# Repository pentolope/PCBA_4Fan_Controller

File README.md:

# Four-Fan PWM/Tach Controller

Board that powers and controls four standard 4-wire 12 V PC fans, with a microcontroller giving independent PWM and tach per fan from a single 12 V input.

This repository holds the design problem for a four-channel PC fan controller. The brief fixes the function and almost nothing else: four standard 4-wire 12 V PC fans are powered and controlled from the board, a microcontroller generates independent PWM and reads independent tach signals, the board accepts a single 12 V input and derives its logic power locally, protection is required, and a simple host interface is to be provided. It also asks that the board be kept compact and serviceable, without stating any dimension, outline, or mounting scheme.

At brief detail 1/5, everything below that statement of function is left to the design agent: microcontroller family, logic rail voltage and regulator topology, host interface protocol and physical connection, how the fans and the 12 V input attach to the board, per-fan current budget, what "sensible protection" concretely covers, board outline, and stackup. Those choices belong in the design record as decisions with rationale, not as requirements attributed to the brief.

> **This board has not been designed.** There is no schematic, no layout and no
> part selection here — only the brief, a reading of the brief, and the
> scaffolding a design run needs. That is the intended state of this repository,
> not a gap in it.

## What the brief fixes, and what it leaves open

The brief pins down 11 requirements and deliberately leaves
17 decisions to whoever designs the board. The `Source` column says
which is which: `brief` is quoted from [BRIEF.md](BRIEF.md), `metadata` comes
from the benchmark catalogue, and `open` means the brief does not fix it.

| Aspect | Value | Source |
|---|---|---|
| Fan channels | Four standard 4-wire 12 V PC fans, powered and controlled by the board | brief |
| Fan control signals | Independent PWM per fan (four independent PWM outputs) | brief |
| Fan feedback signals | Independent tach read per fan (four independent tach inputs) | brief |
| Control element | A microcontroller performs PWM generation and tach reading; no family, package, or vendor named | brief |
| Power input | A single 12 V input, accepted by the board; the brief fixes one 12 V input and says nothing about whether anything else (for example the host link) also supplies power | brief |
| Logic power | Derived locally on the board rather than supplied externally; rail voltage and conversion method not stated | brief |
| Protection | Protection is required; the brief says only "sensible" and names no fault modes or devices | brief |
| Host interface | A simple host interface is to be provided; protocol, physical layer, and physical connection not specified | brief |
| Mechanical intent | Compact and serviceable; no dimensions, outline, mounting pattern, or enclosure stated | brief |
| Likely layer count | 2 | metadata |
| Category / difficulty / brief detail | mixed-power-digital; difficulty 2/5; detail 1/5 | metadata |
| Primary stressors | PWM/tach routing, 12V distribution, connector density, power thermal | metadata |
| Microcontroller, regulator, and connector selection | Not fixed by the brief — design agent's choice, to be justified in the design record | open |
| Board outline, stackup, and 12 V current budget | Not fixed by the brief — design agent's choice; no size, copper weight, or per-fan current is stated | open |
| Whether any supply other than the 12 V input exists | Not fixed by the brief — one 12 V input is fixed and logic power must be derived locally, but the brief does not say whether the host connection or a programming/bring-up link may also carry power; the design agent decides and records this | open |

The full split, with the verbatim brief text substantiating every fixed
requirement, is in [board/requirements.md](board/requirements.md) and
machine-readably in [board/requirements.json](board/requirements.json).

**Missing details are design freedom, not permission to fabricate unstated user
requirements.** A choice the brief left open is recorded as a decision, with its
reasoning — never promoted into a requirement.

## Benchmark position

| | |
|---|---|
| Benchmark id | 4 of 32 |
| Category | mixed-power-digital |
| Difficulty | 2 / 5 |
| Brief detail | 1 / 5 |
| Likely layer count | 2 |
| Primary stressors | PWM/tach routing, 12V distribution, connector density, power thermal |

This is a mixed-power-digital board at difficulty 2/5 with a detail 1/5 brief — a modest circuit whose difficulty lies in the interface between a 12 V power path and low-voltage digital control on a likely 2-layer stackup. The named stressors are PWM/tach routing, 12V distribution, connector density, and power thermal: four fan connections plus the 12 V input and the host interface all have to land on a board the brief asks to keep "compact", whatever connector scheme is chosen, while eight switching and feedback signals route alongside the fan current path. Because the brief specifies function but no parts, voltages, currents, or geometry, it primarily tests whether an agent can carry a thin brief forward with documented engineering decisions instead of back-filling invented user requirements.

This repository is one of thirty-two. The suite, the protocol and the results
live in [PCBA_AutoDesignAndTest_Bench](https://github.com/pentolope/PCBA_AutoDesignAndTest_Bench).

## Repository layout

| Path | Contents |
|---|---|
| `BRIEF.md` | the supplied brief — authoritative, preserved byte for byte, never edited |
| `board/requirements.md` | what the brief fixes, what it leaves open, and where decisions get recorded |
| `board/requirements.json` | the same split, machine-readable, each fixed requirement bound to brief text |
| `board/manifest.template.json` | the toolkit's minimum manifest, pre-filled for this board |
| `board/toolchain.json` | where this board's build finds KiCad and the router |
| `benchmark/metadata.json` | the supplied catalogue entry — category, difficulty, detail, stressors |
| `docs/architecture.md` | the decisions this board must make, as questions, unanswered |
| `docs/sources.md` | the classes of evidence the design will have to cite |
| `docs/status.md` | what exists, what does not, and what is deliberately absent |
| `candidates/` | disposable search output, ignored by Git |
| `.claude/skills/` | the accountability-review skill [CLAUDE.md](CLAUDE.md) requires before a push |
| `tooling/PCBA_AutoDesignAndTest` | the shared verification/routing/release toolkit, as a pinned submodule |

## Getting the repository

The toolkit is a submodule and carries KiCad Routing Tools as a submodule of its
own, so clone recursively:

```bash
git clone --recursive https://github.com/pentolope/PCBA_4Fan_Controller.git
```

```bash
git submodule update --init --recursive
```

## Designing the board

Generic verification, routing and release logic is **not** written here. It is
consumed from `tooling/PCBA_AutoDesignAndTest`, which is board-agnostic by
construction and must stay that way; this repository owns the board and nothing
else. Start from
[the toolkit's onboarding guide](tooling/PCBA_AutoDesignAndTest/examples/onboarding.md),
and see [CLAUDE.md](CLAUDE.md) for the rules a design run works under.

```bash
python3 tooling/PCBA_AutoDesignAndTest/run.py preflight
```

## Brief integrity

`BRIEF.md` SHA-256 `531862b585105d510d5cae2a7e9f812644b966f14cebd01fc22d28720cdb2ca3`

Every quotation in `board/requirements.json` is bound to those exact bytes. If
the brief ever changes, the bindings are stale by construction — which is the
point of recording the digest.

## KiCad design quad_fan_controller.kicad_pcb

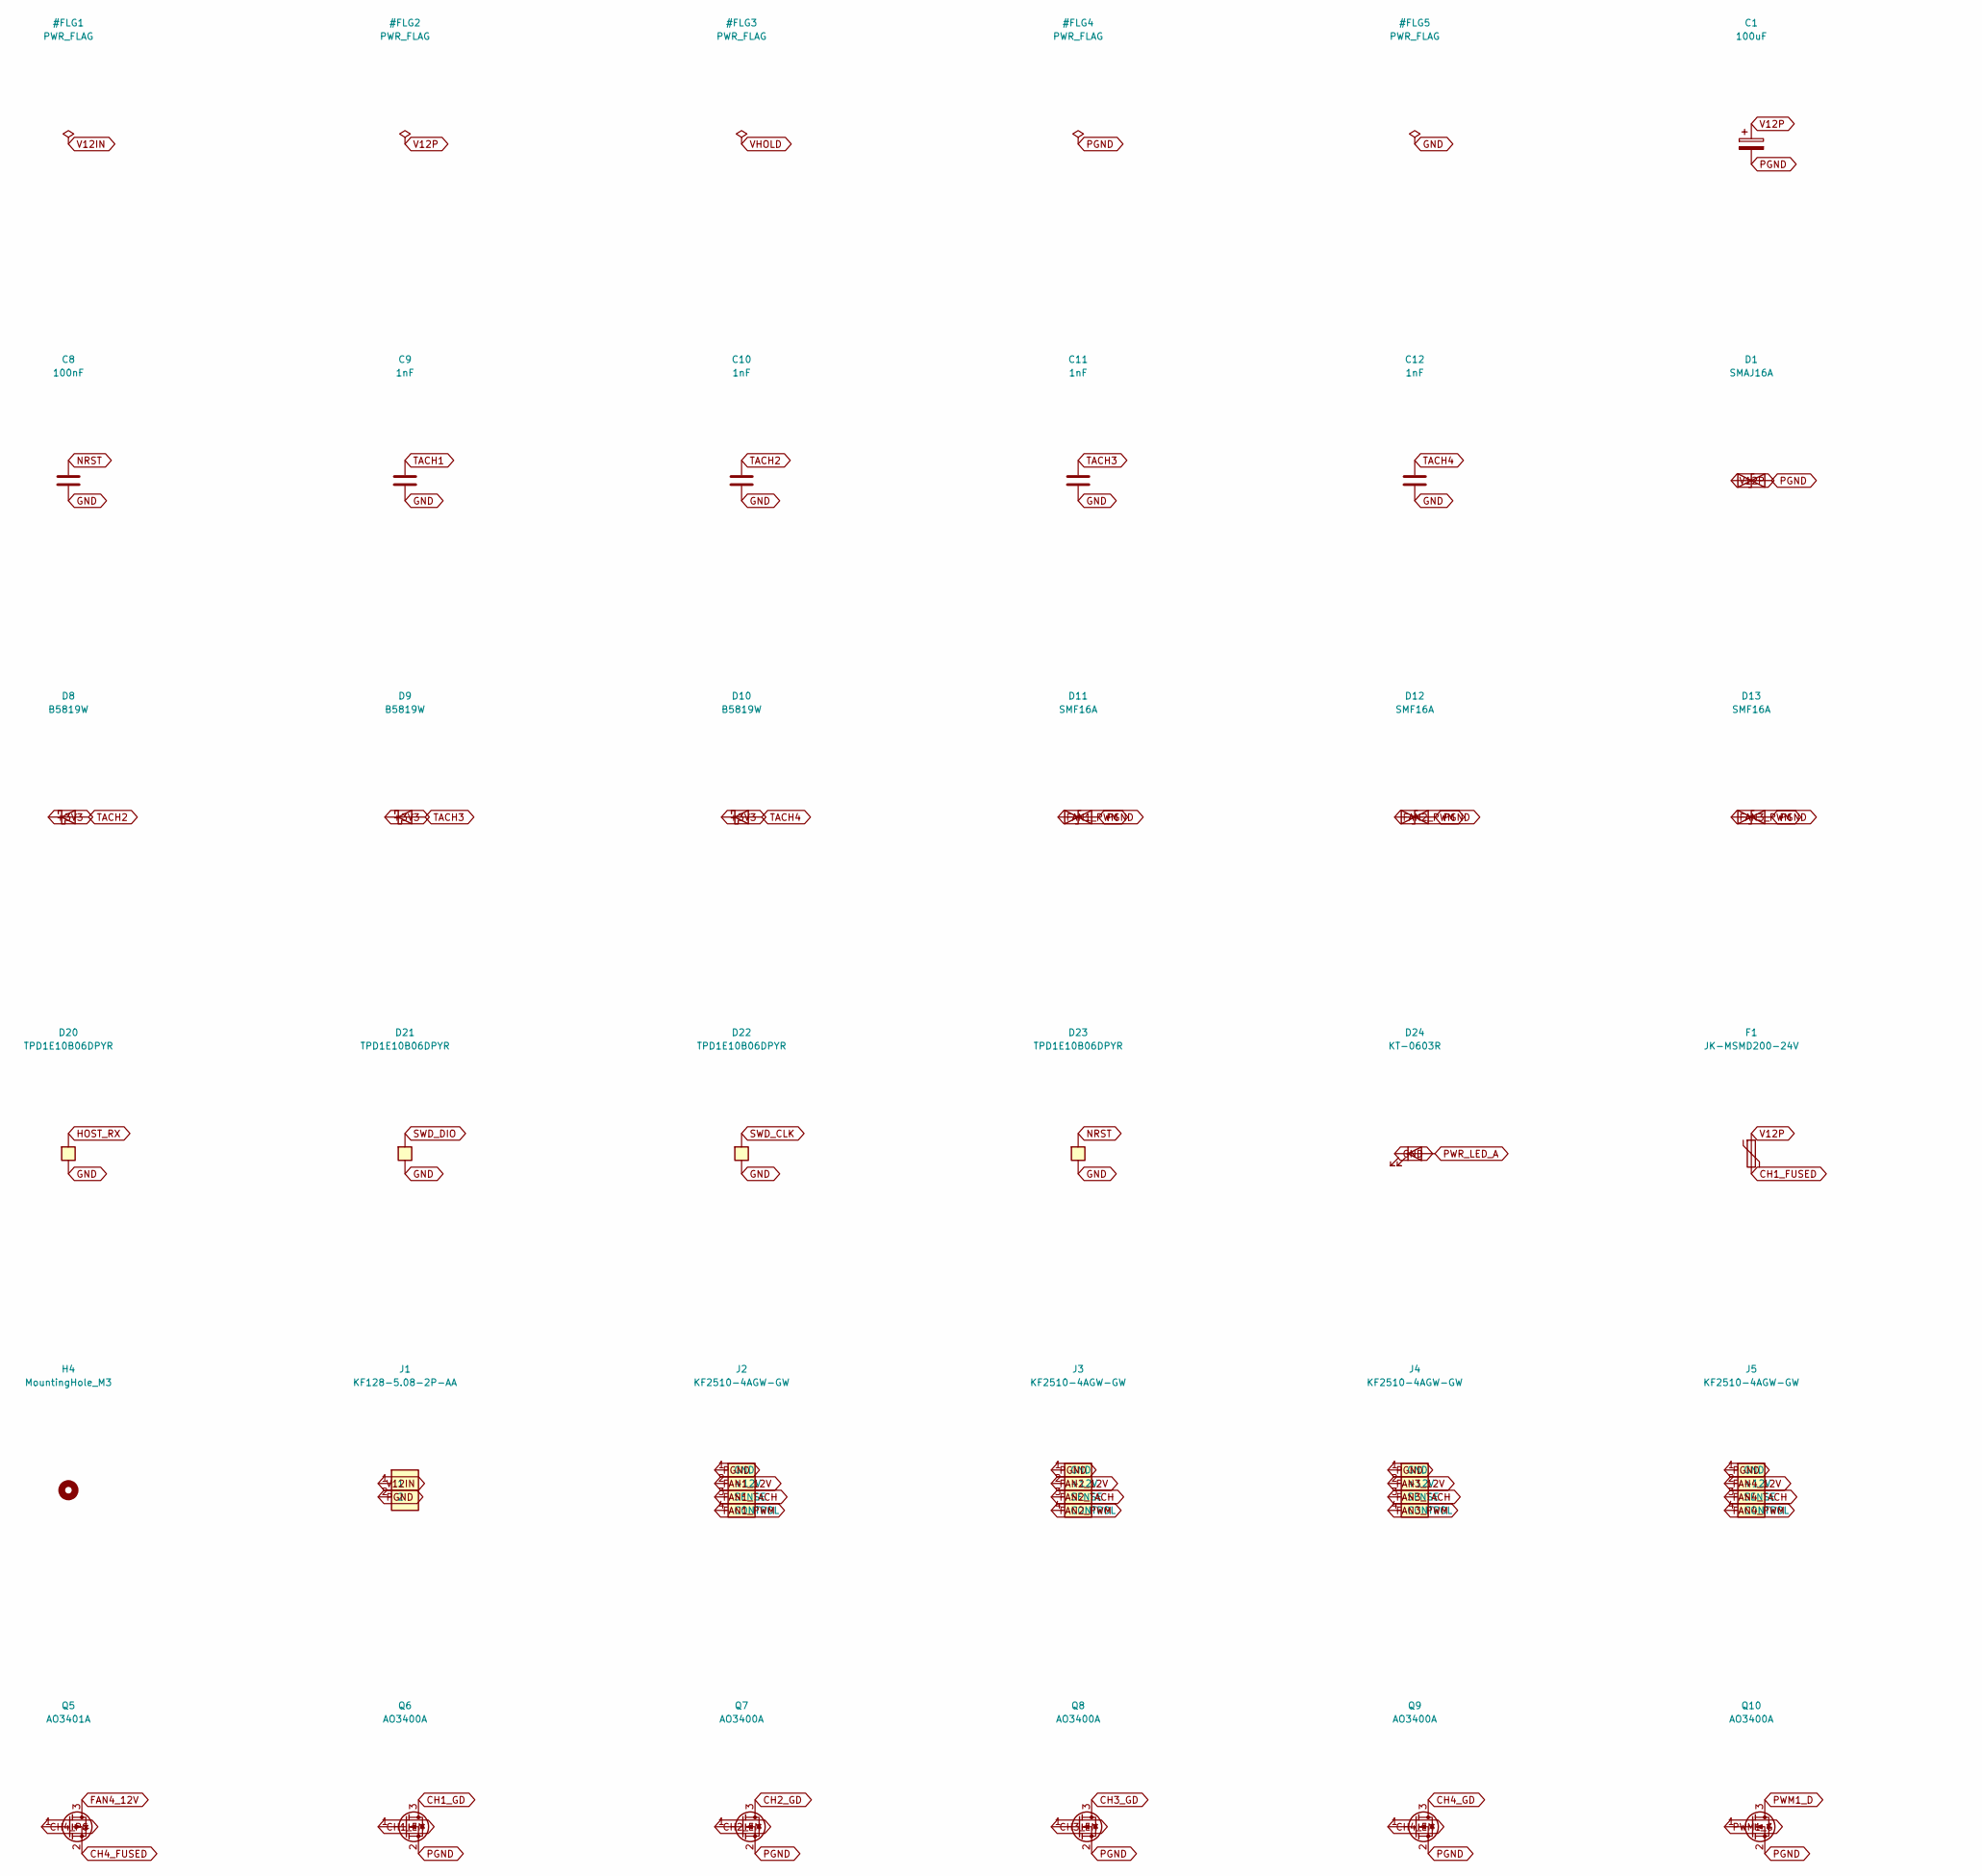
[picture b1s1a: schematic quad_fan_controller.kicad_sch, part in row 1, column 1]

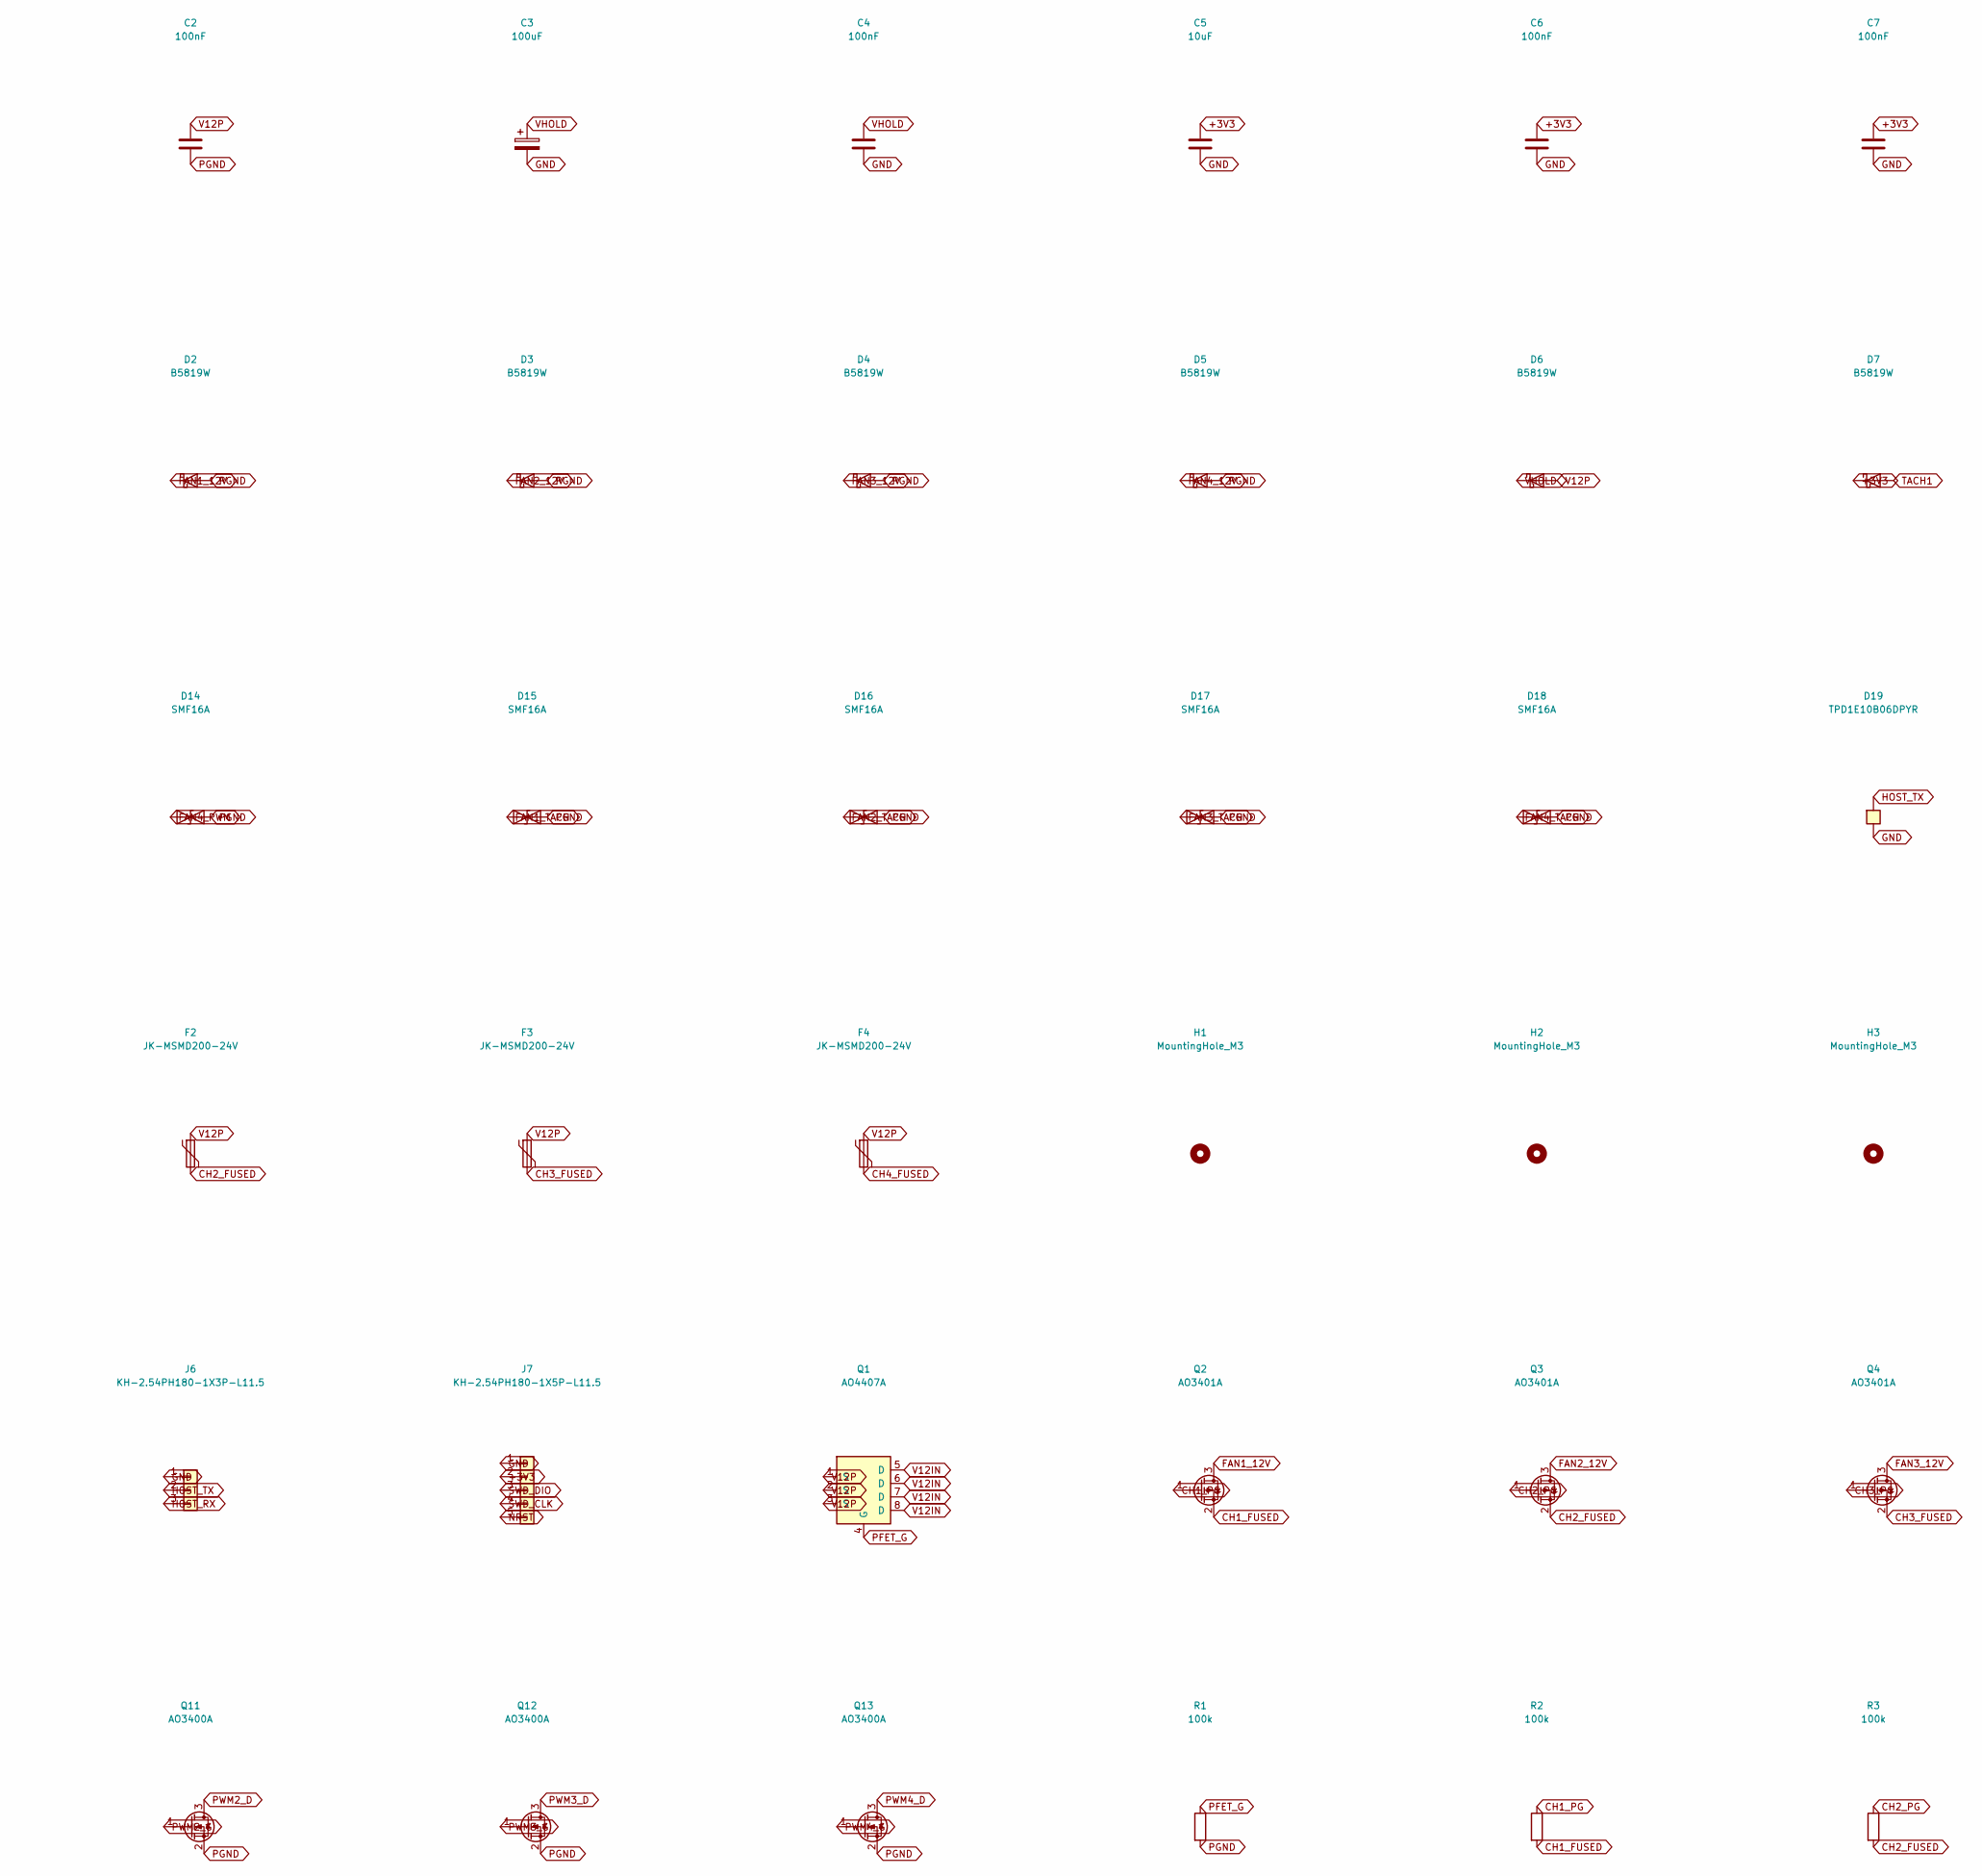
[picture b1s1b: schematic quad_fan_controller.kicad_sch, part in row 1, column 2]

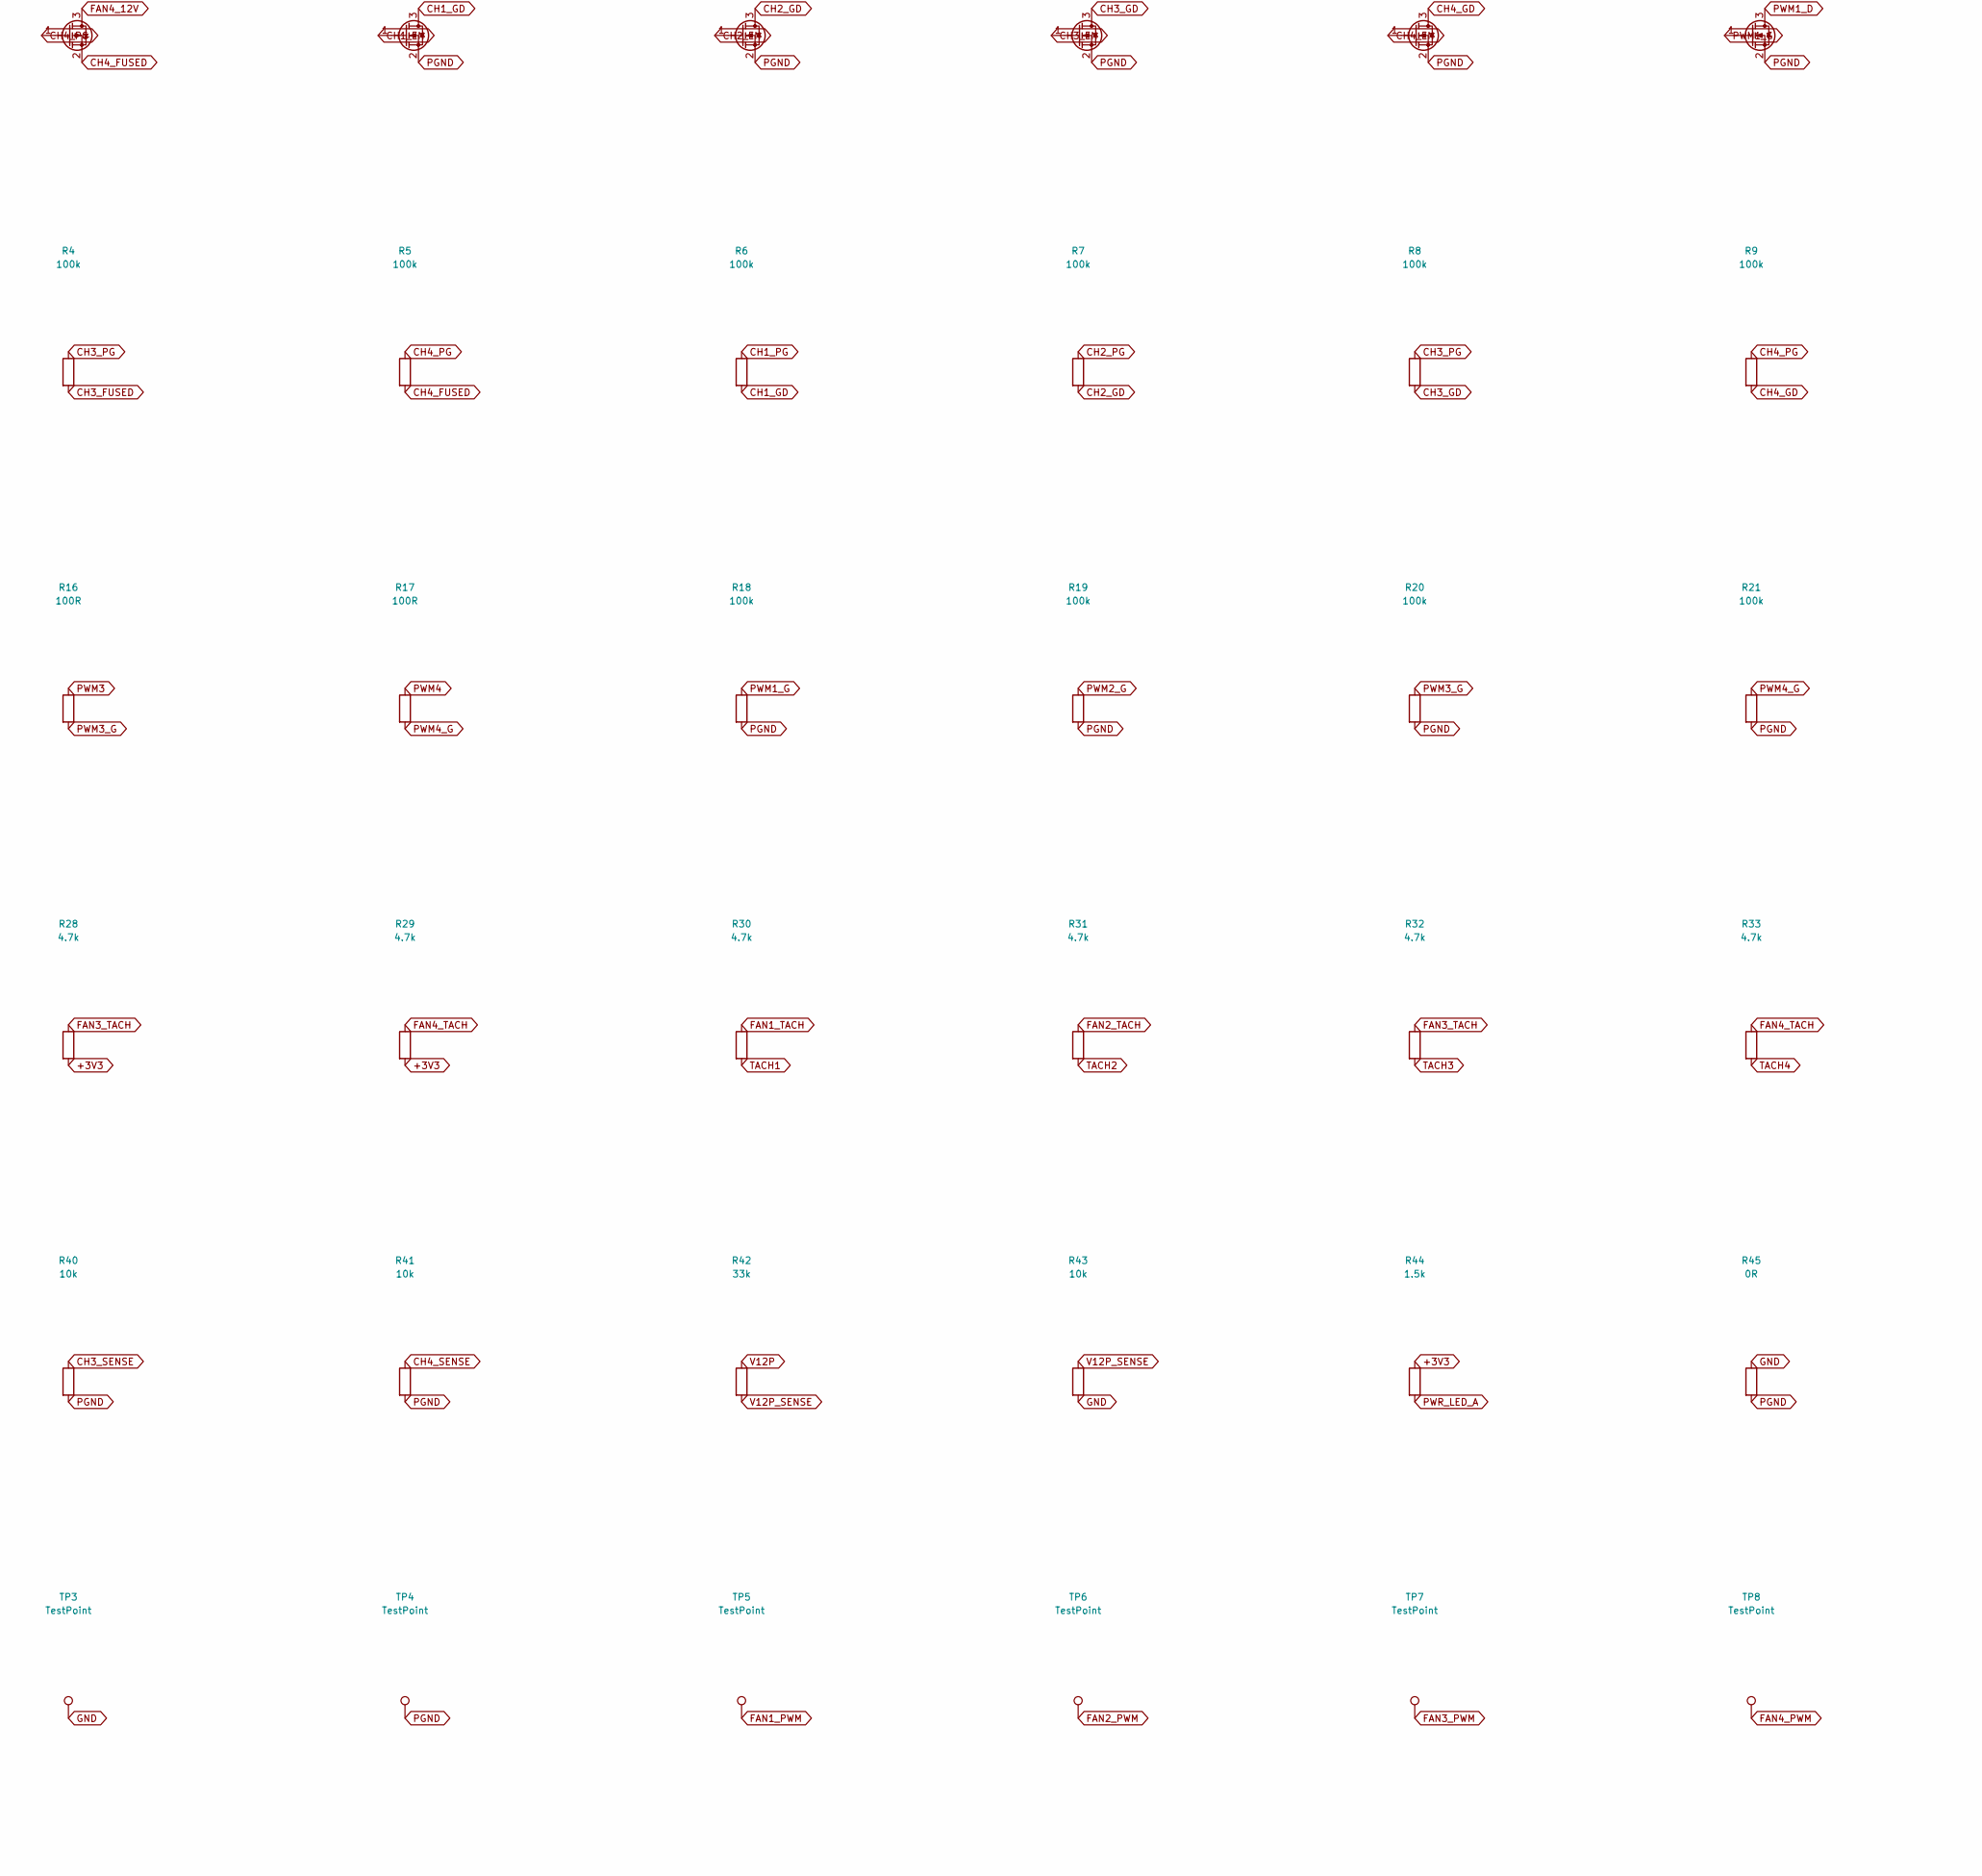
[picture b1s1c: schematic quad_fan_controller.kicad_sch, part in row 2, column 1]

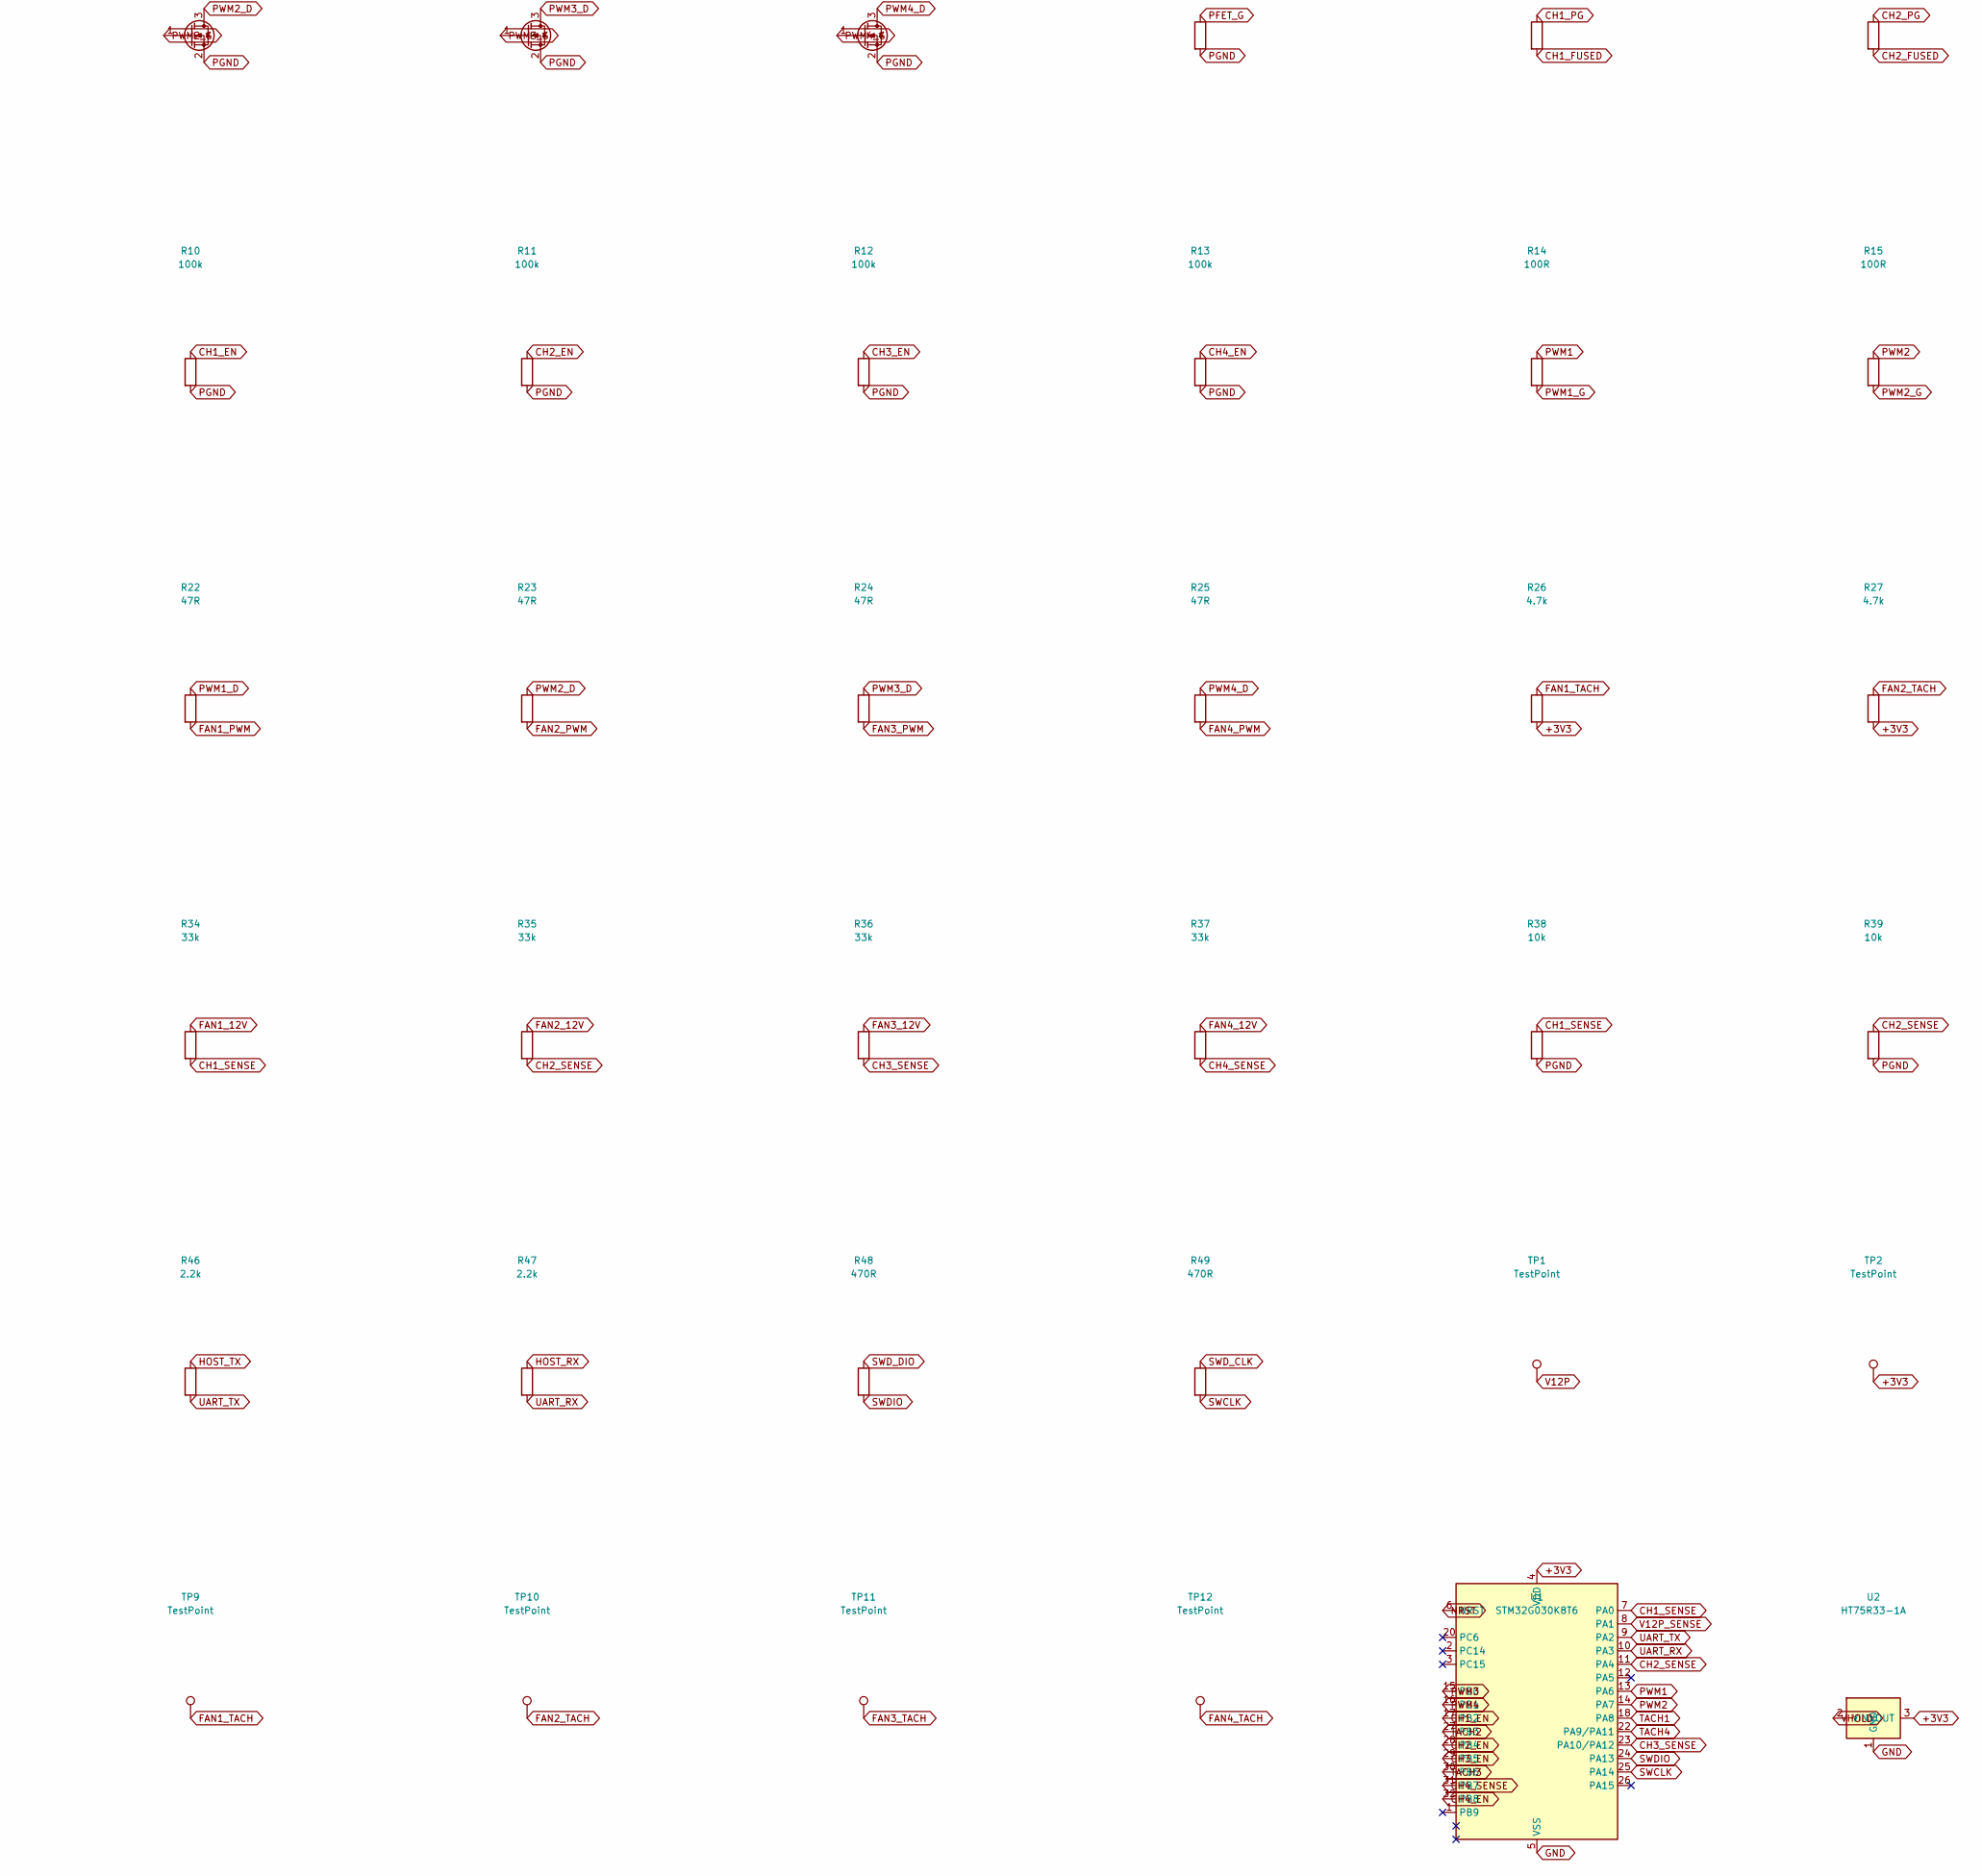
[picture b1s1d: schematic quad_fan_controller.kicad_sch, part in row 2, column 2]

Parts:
C1, C3: 100uF; CP_Elec_6.3x7.7; MPN RVT100UF25V67RV0011; LCSC C2836443
C2, C4, C6, C7, C8: 100nF; C_0603_1608Metric; MPN CC0603KRX7R9BB104; LCSC C14663
C5: 10uF; C_0805_2012Metric; MPN CL21A106KAYNNNE; LCSC C15850
C9, C10, C11, C12: 1nF; C_0603_1608Metric; MPN CC0603KRX7R9BB102; LCSC C100040
D1: SMAJ16A; D_SMA; MPN SMAJ16A; LCSC C74561
D2, D3, D4, D5, D6, D7, D8, D9, D10: B5819W; D_SOD-123; MPN B5819W SL; LCSC C8598
D11, D12, D13, D14, D15, D16, D17, D18: SMF16A; D_SOD-123FL_1.2x1.2mm_P3.2mm; MPN SMF16A; LCSC C353308
D19, D20, D21, D22, D23: TPD1E10B06DPYR; TI_X1SON-2_1.0x0.6mm_P0.65mm; MPN TPD1E10B06DPYR; LCSC C48260
D24: KT-0603R; LED_0603_1608Metric; MPN KT-0603R; LCSC C2286
F1, F2, F3, F4: JK-MSMD200-24V; PTC_1812_Jinrui_JK-mSMD; MPN JK-MSMD200-24V; LCSC C561584
H1, H2, H3, H4: MountingHole_M3; MountingHole_3.2mm_M3
J1: KF128-5.08-2P-AA; TerminalBlock_KF128-5.08_1x02_P5.08mm; MPN KF128-5.08-2P-AA; LCSC C474952
J2, J3, J4, J5: KF2510-4AGW-GW; FanHeader_2510_1x04_P2.54mm_Horizontal; MPN KF2510-4AGW-GW; LCSC C722747
J6: KH-2.54PH180-1X3P-L11.5; PinHeader_1x03_P2.54mm_Vertical; MPN KH-2.54PH180-1X3P-L11.5; LCSC C2932698
J7: KH-2.54PH180-1X5P-L11.5; PinHeader_1x05_P2.54mm_Vertical; MPN KH-2.54PH180-1X5P-L11.5; LCSC C2932699
Q1: AO4407A; SOIC-8_3.9x4.9mm_P1.27mm; MPN AO4407A; LCSC C16072
Q2, Q3, Q4, Q5: AO3401A; SOT-23; MPN AO3401A; LCSC C15127
Q6, Q7, Q8, Q9, Q10, Q11, Q12, Q13: AO3400A; SOT-23; MPN AO3400A; LCSC C20917
R1, R2, R3, R4, R5, R6, R7, R8, R9, R10, R11, R12, R13, R18, R19, R20, R21: 100k; R_0603_1608Metric; MPN 0603WAF1003T5E; LCSC C25803
R14, R15, R16, R17: 100R; R_0603_1608Metric; MPN 0603WAF1000T5E; LCSC C22775
R22, R23, R24, R25: 47R; R_0603_1608Metric; MPN 0603WAF470JT5E; LCSC C23182
R26, R27, R28, R29, R30, R31, R32, R33: 4.7k; R_0603_1608Metric; MPN 0603WAF4701T5E; LCSC C23162
R34, R35, R36, R37, R42: 33k; R_0603_1608Metric; MPN 0603WAF3302T5E; LCSC C4216
R38, R39, R40, R41, R43: 10k; R_0603_1608Metric; MPN 0603WAF1002T5E; LCSC C25804
R44: 1.5k; R_0603_1608Metric; MPN 0603WAF1501T5E; LCSC C22843
R45: 0R; R_0603_1608Metric; MPN 0603WAF0000T5E; LCSC C21189
R46, R47: 2.2k; R_0603_1608Metric; MPN 0603WAF2201T5E; LCSC C4190
R48, R49: 470R; R_0603_1608Metric; MPN 0603WAF4700T5E; LCSC C23179
TP1, TP2, TP3, TP4, TP5, TP6, TP7, TP8, TP9, TP10, TP11, TP12: TestPoint; TestPoint_Pad_D1.0mm
U1: STM32G030K8T6; LQFP-32_7x7mm_P0.8mm; MPN STM32G030K8T6TR; LCSC C724044
U2: HT75R33-1A; SOT-89-3; MPN HT75R33-1A; LCSC C53223865

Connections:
+3V3: C5.1, C6.1, C7.1, D7.1 (K), D8.1 (K), D9.1 (K), D10.1 (K), J7.2, R26.2, R27.2, R28.2, R29.2, R44.1, TP2.1, U1.4 (VDD), U2.3 (VOUT)
CH1_EN: Q6.1 (G), R10.1, U1.17 (PB2)
CH1_FUSED: F1.2, Q2.2 (S), R2.2
CH1_GD: Q6.3 (D), R6.2
CH1_PG: Q2.1 (G), R2.1, R6.1
CH1_SENSE: R34.2, R38.1, U1.7 (PA0)
CH2_EN: Q7.1 (G), R11.1, U1.28 (PB4)
CH2_FUSED: F2.2, Q3.2 (S), R3.2
CH2_GD: Q7.3 (D), R7.2
CH2_PG: Q3.1 (G), R3.1, R7.1
CH2_SENSE: R35.2, R39.1, U1.11 (PA4)
CH3_EN: Q8.1 (G), R12.1, U1.29 (PB5)
CH3_FUSED: F3.2, Q4.2 (S), R4.2
CH3_GD: Q8.3 (D), R8.2
CH3_PG: Q4.1 (G), R4.1, R8.1
CH3_SENSE: R36.2, R40.1, U1.23 (PA10/PA12)
CH4_EN: Q9.1 (G), R13.1, U1.32 (PB8)
CH4_FUSED: F4.2, Q5.2 (S), R5.2
CH4_GD: Q9.3 (D), R9.2
CH4_PG: Q5.1 (G), R5.1, R9.1
CH4_SENSE: R37.2, R41.1, U1.31 (PB7)
FAN1_12V: D2.1 (K), J2.2 (+12V), Q2.3 (D), R34.1
FAN1_PWM: D11.1 (A1), J2.4 (CONTROL), R22.2, TP5.1
FAN1_TACH: D15.1 (A1), J2.3 (SENSE), R26.1, R30.1, TP9.1
FAN2_12V: D3.1 (K), J3.2 (+12V), Q3.3 (D), R35.1
FAN2_PWM: D12.1 (A1), J3.4 (CONTROL), R23.2, TP6.1
FAN2_TACH: D16.1 (A1), J3.3 (SENSE), R27.1, R31.1, TP10.1
FAN3_12V: D4.1 (K), J4.2 (+12V), Q4.3 (D), R36.1
FAN3_PWM: D13.1 (A1), J4.4 (CONTROL), R24.2, TP7.1
FAN3_TACH: D17.1 (A1), J4.3 (SENSE), R28.1, R32.1, TP11.1
FAN4_12V: D5.1 (K), J5.2 (+12V), Q5.3 (D), R37.1
FAN4_PWM: D14.1 (A1), J5.4 (CONTROL), R25.2, TP8.1
FAN4_TACH: D18.1 (A1), J5.3 (SENSE), R29.1, R33.1, TP12.1
GND: C3.2, C4.2, C5.2, C6.2, C7.2, C8.2, C9.2, C10.2, C11.2, C12.2, D19.1 (A1), D20.1 (A1), D21.1 (A1), D22.1 (A1), D23.1 (A1), D24.1 (K), J6.1, J7.1, R43.2, R45.1, TP3.1, U1.5 (VSS), U2.1 (GND)
HOST_RX: D20.2 (A2), J6.3, R47.1
HOST_TX: D19.2 (A2), J6.2, R46.1
NRST: C8.1, D23.2 (A2), J7.5, U1.6 (NRST)
PFET_G: Q1.4 (G), R1.1
PGND: C1.2, C2.2, D1.2 (A2), D2.2 (A), D3.2 (A), D4.2 (A), D5.2 (A), D11.2 (A2), D12.2 (A2), D13.2 (A2), D14.2 (A2), D15.2 (A2), D16.2 (A2), D17.2 (A2), D18.2 (A2), J1.2, J2.1 (GND), J3.1 (GND), J4.1 (GND), J5.1 (GND), Q6.2 (S), Q7.2 (S), Q8.2 (S), Q9.2 (S), Q10.2 (S), Q11.2 (S), Q12.2 (S), Q13.2 (S), R1.2, R10.2, R11.2, R12.2, R13.2, R18.2, R19.2, R20.2, R21.2, R38.2, R39.2, R40.2, R41.2, R45.2, TP4.1
PWM1: R14.1, U1.13 (PA6)
PWM1_D: Q10.3 (D), R22.1
PWM1_G: Q10.1 (G), R14.2, R18.1
PWM2: R15.1, U1.14 (PA7)
PWM2_D: Q11.3 (D), R23.1
PWM2_G: Q11.1 (G), R15.2, R19.1
PWM3: R16.1, U1.15 (PB0)
PWM3_D: Q12.3 (D), R24.1
PWM3_G: Q12.1 (G), R16.2, R20.1
PWM4: R17.1, U1.16 (PB1)
PWM4_D: Q13.3 (D), R25.1
PWM4_G: Q13.1 (G), R17.2, R21.1
PWR_LED_A: D24.2 (A), R44.2
SWCLK: R49.2, U1.25 (PA14)
SWDIO: R48.2, U1.24 (PA13)
SWD_CLK: D22.2 (A2), J7.4, R49.1
SWD_DIO: D21.2 (A2), J7.3, R48.1
TACH1: C9.1, D7.2 (A), R30.2, U1.18 (PA8)
TACH2: C10.1, D8.2 (A), R31.2, U1.27 (PB3)
TACH3: C11.1, D9.2 (A), R32.2, U1.30 (PB6)
TACH4: C12.1, D10.2 (A), R33.2, U1.22 (PA9/PA11)
UART_RX: R47.2, U1.10 (PA3)
UART_TX: R46.2, U1.9 (PA2)
V12IN: J1.1, Q1.5 (D), Q1.6 (D), Q1.7 (D), Q1.8 (D)
V12P: C1.1, C2.1, D1.1 (A1), D6.2 (A), F1.1, F2.1, F3.1, F4.1, Q1.1 (S), Q1.2 (S), Q1.3 (S), R42.1, TP1.1
V12P_SENSE: R42.2, R43.1, U1.8 (PA1)
VHOLD: C3.1, C4.1, D6.1 (K), U2.2 (VIN)

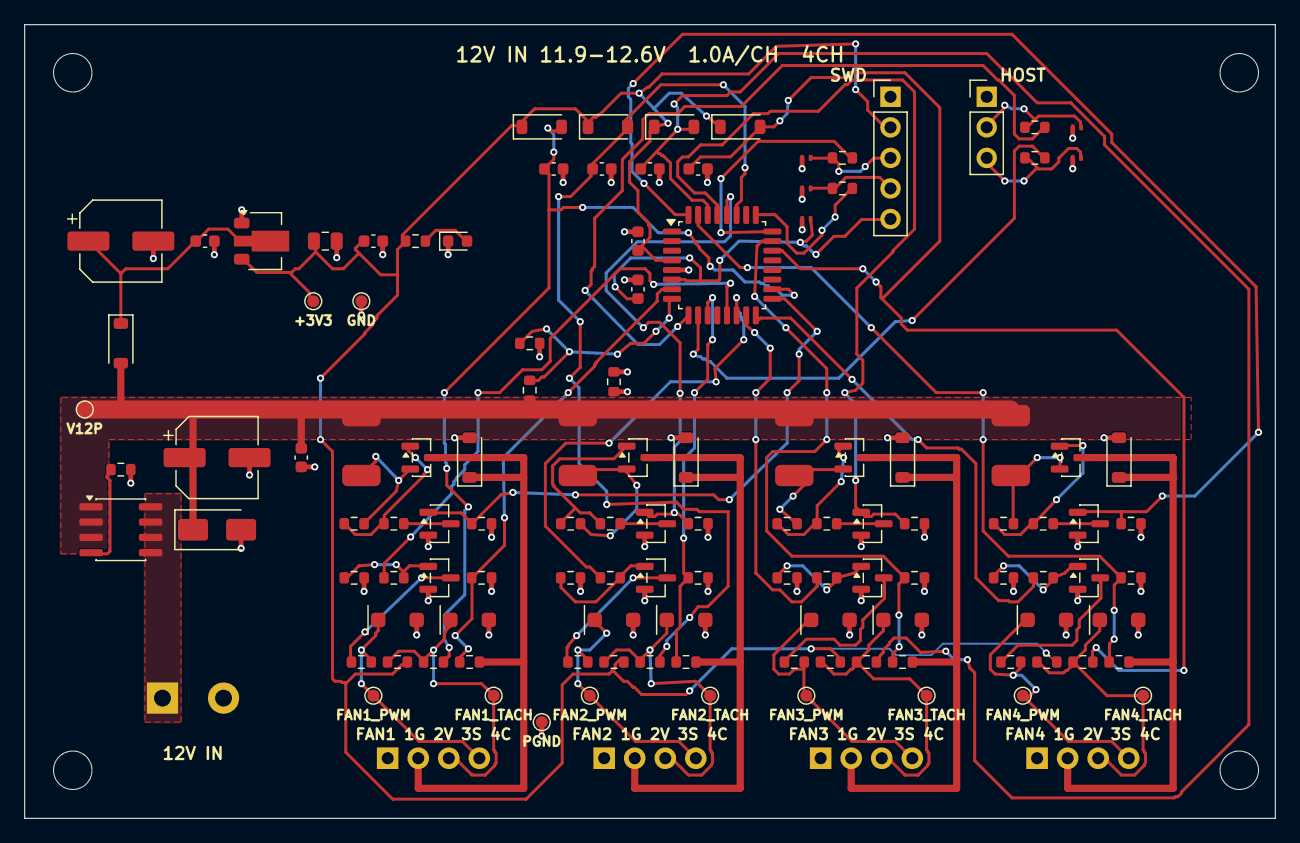
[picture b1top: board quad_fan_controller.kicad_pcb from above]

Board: 2 copper layers, 104.0 x 66.0 mm, 127 parts (0 on the bottom side), 66 nets.
